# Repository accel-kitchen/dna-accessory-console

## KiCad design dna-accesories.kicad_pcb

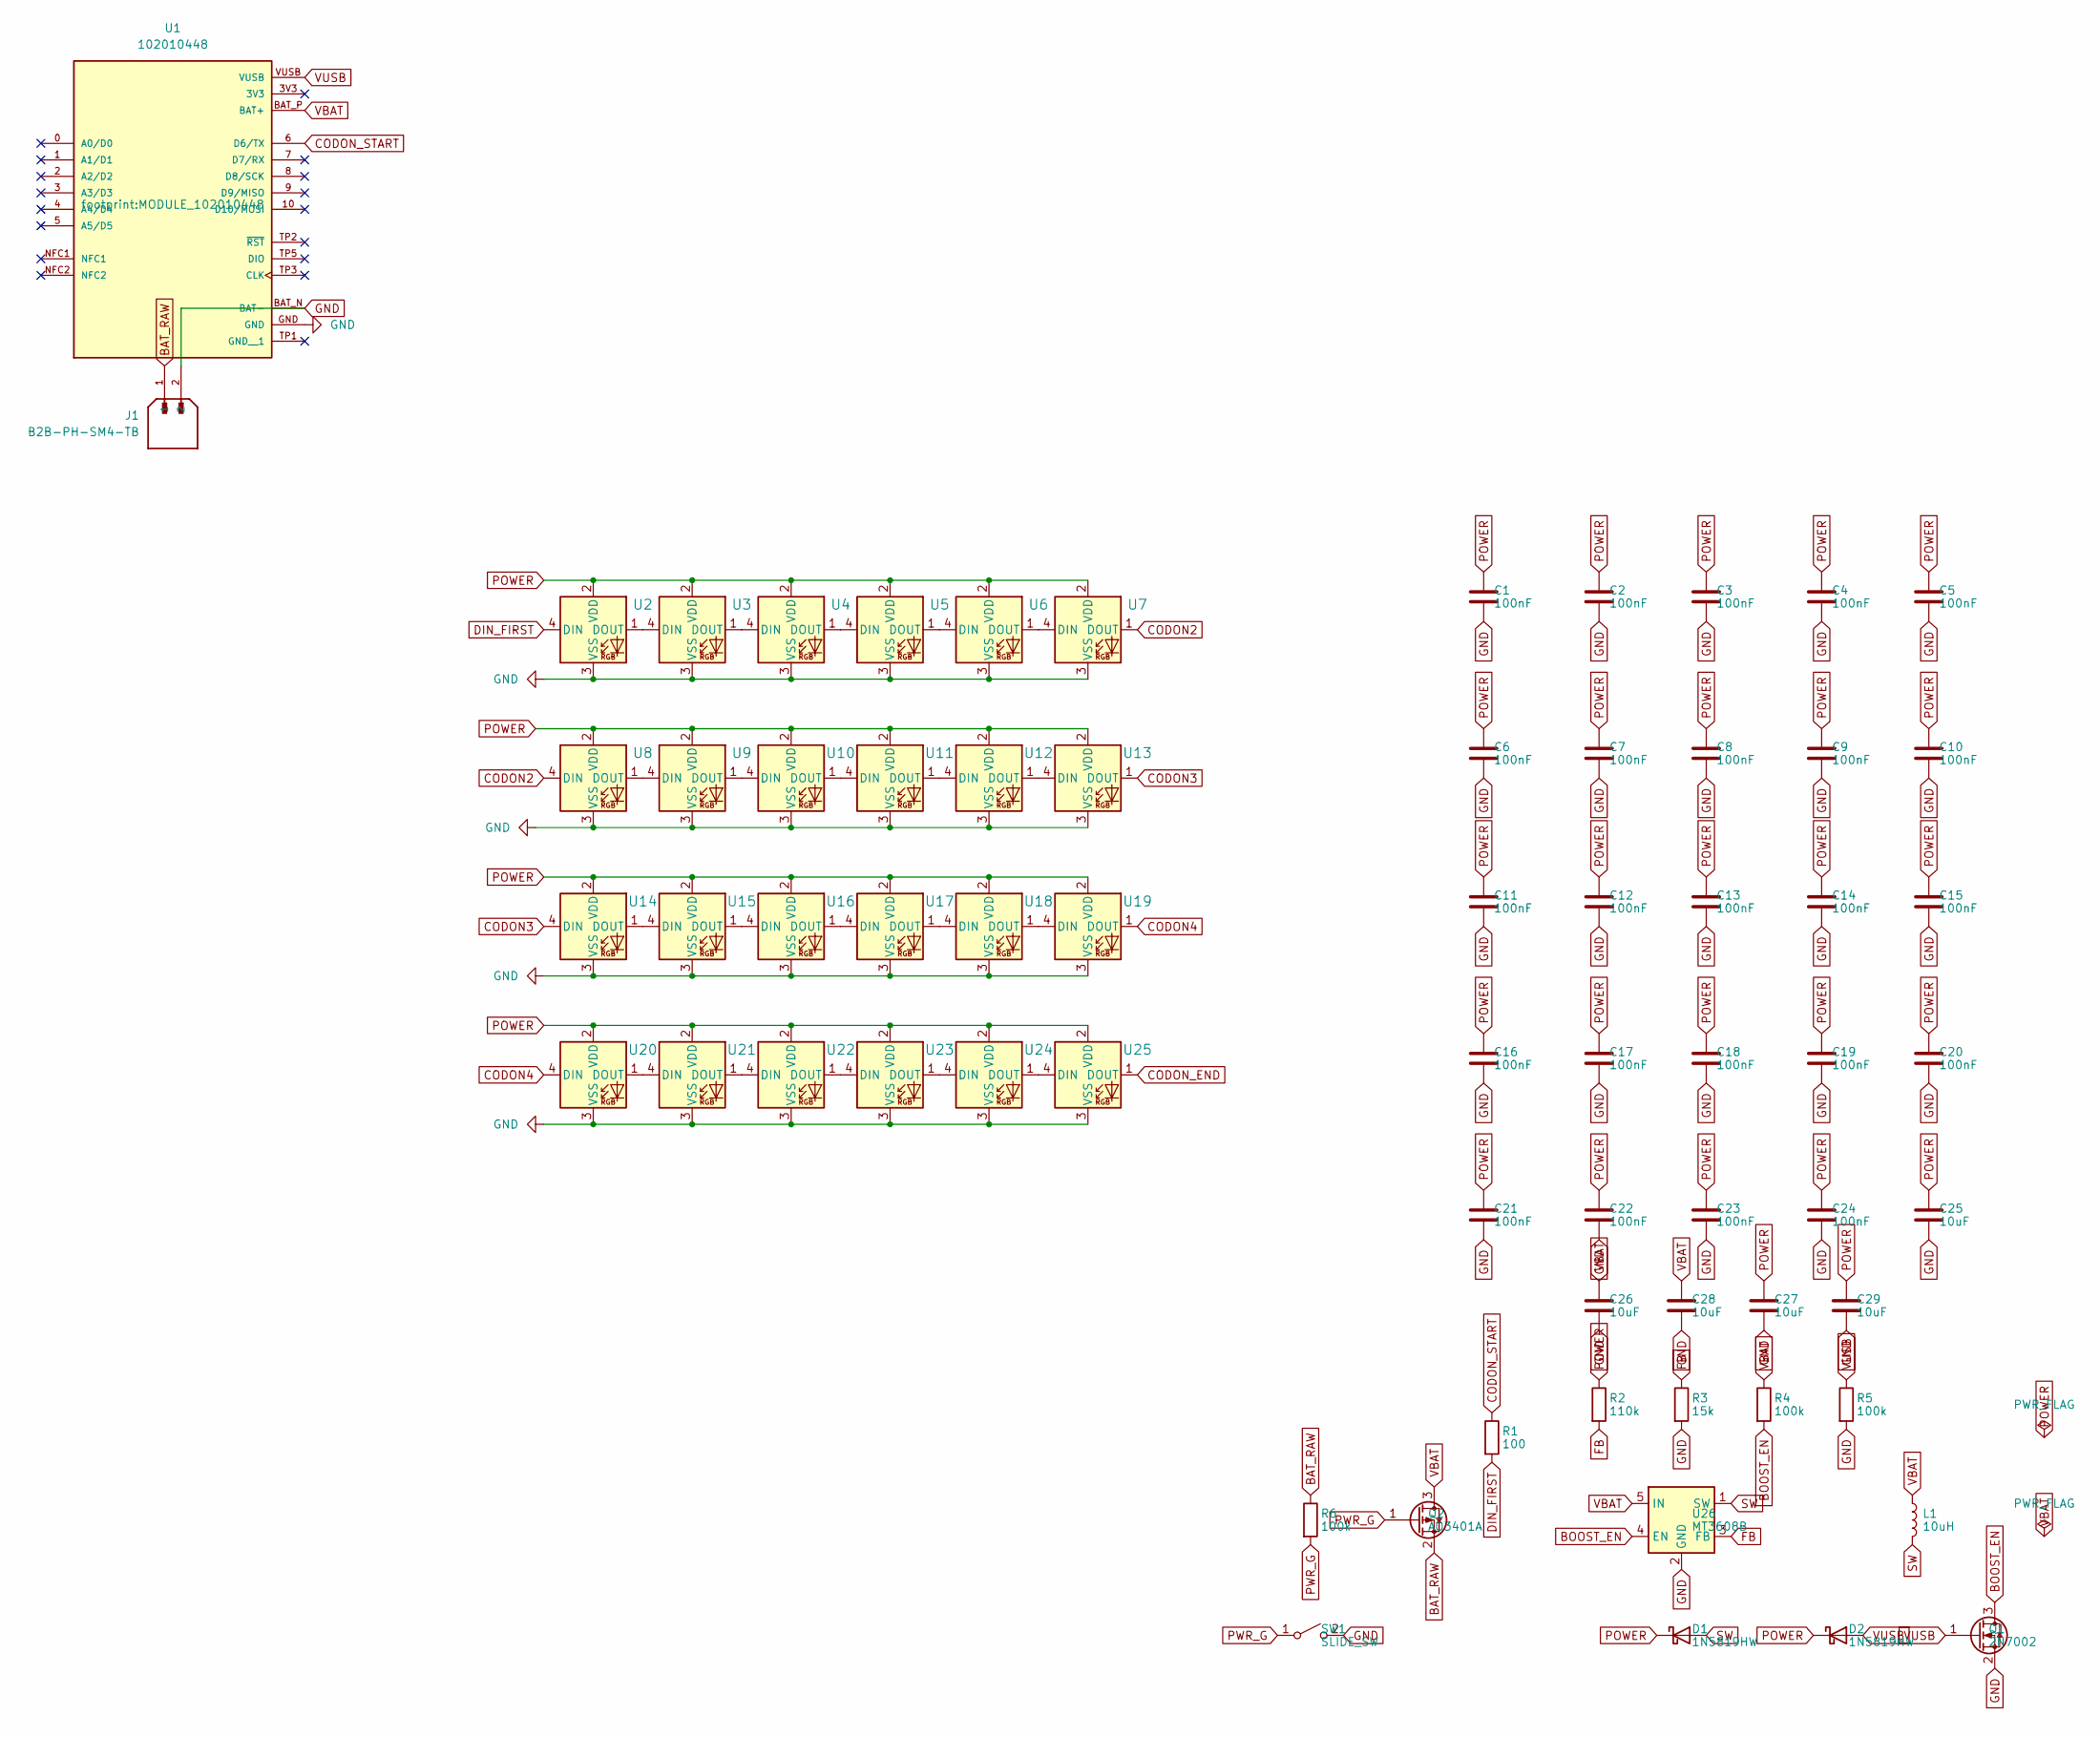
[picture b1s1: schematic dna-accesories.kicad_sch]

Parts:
C1, C2, C3, C4, C5, C6, C7, C8, C9, C10, C11, C12, C13, C14, C15, C16, C17, C18, C19, C20, C21, C22, C23, C24: 100nF; C_0402_1005Metric
C25, C26, C27, C28, C29: 10uF; C_0805_2012Metric
D1, D2: 1N5819HW; D_SOD-123
J1: B2B-PH-SM4-TB; JST_B2B-PH-SM4-TB; PARTREV N/A
L1: 10uH; L_Bourns-SRN4018
Q1: 2N7002; SOT-23
Q2: AO3401A; SOT-23
R1: 100; R_0402_1005Metric
R2: 110k; R_0402_1005Metric
R3: 15k; R_0402_1005Metric
R4, R5, R6: 100k; R_0402_1005Metric
SW1: SLIDE_SW; SW_DIP_SPSTx01_Slide_Copal_CHS-01A_W5.08mm_P1.27mm_JPin
U1: 102010448; MODULE_102010448; PARTREV 2022/08/18
U2, U3, U4, U5, U6, U7, U8, U9, U10, U11, U12, U13, U14, U15, U16, U17, U18, U19, U20, U21, U22, U23, U24, U25: XL-1010RGBC-WS2812B; SMD4_XL-1010RGBC_XLG
U26: MT3608B; SOT-23-6

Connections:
BAT_RAW: J1.1, Q2.2 (S), R6.1
BOOST_EN: Q1.3 (D), R4.2, U26.4 (EN)
CODON2: U7.1 (VDD), U8.4 (DIN)
CODON3: U13.1 (VDD), U14.4 (DIN)
CODON4: U19.1 (VDD), U20.4 (DIN)
CODON_END: U25.1 (VDD)
CODON_START: R1.1, U1.6 (D6/TX)
DIN_FIRST: R1.2, U2.4 (DIN)
FB: R2.2, R3.1, U26.3 (FB)
GND: C1.2, C2.2, C3.2, C4.2, C5.2, C6.2, C7.2, C8.2, C9.2, C10.2, C11.2, C12.2, C13.2, C14.2, C15.2, C16.2, C17.2, C18.2, C19.2, C20.2, C21.2, C22.2, C23.2, C24.2, C25.2, C26.2, C27.2, C28.2, C29.2, J1.2, Q1.2 (S), R3.2, R5.2, SW1.2 (B), U1.BAT_N (BAT-), U1.GND, U2.3 (VSS), U3.3 (VSS), U4.3 (VSS), U5.3 (VSS), U6.3 (VSS), U7.3 (VSS), U8.3 (VSS), U9.3 (VSS), U10.3 (VSS), U11.3 (VSS), U12.3 (VSS), U13.3 (VSS), U14.3 (VSS), U15.3 (VSS), U16.3 (VSS), U17.3 (VSS), U18.3 (VSS), U19.3 (VSS), U20.3 (VSS), U21.3 (VSS), U22.3 (VSS), U23.3 (VSS), U24.3 (VSS), U25.3 (VSS), U26.2 (GND)
unnamed: U2.1 (VDD), U3.4 (DIN)
unnamed: U3.1 (VDD), U4.4 (DIN)
unnamed: U4.1 (VDD), U5.4 (DIN)
unnamed: U5.1 (VDD), U6.4 (DIN)
unnamed: U6.1 (VDD), U7.4 (DIN)
unnamed: U8.1 (VDD), U9.4 (DIN)
unnamed: U9.1 (VDD), U10.4 (DIN)
unnamed: U10.1 (VDD), U11.4 (DIN)
unnamed: U11.1 (VDD), U12.4 (DIN)
unnamed: U12.1 (VDD), U13.4 (DIN)
unnamed: U14.1 (VDD), U15.4 (DIN)
unnamed: U15.1 (VDD), U16.4 (DIN)
unnamed: U16.1 (VDD), U17.4 (DIN)
unnamed: U17.1 (VDD), U18.4 (DIN)
unnamed: U18.1 (VDD), U19.4 (DIN)
unnamed: U20.1 (VDD), U21.4 (DIN)
unnamed: U21.1 (VDD), U22.4 (DIN)
unnamed: U22.1 (VDD), U23.4 (DIN)
unnamed: U23.1 (VDD), U24.4 (DIN)
unnamed: U24.1 (VDD), U25.4 (DIN)
POWER: C1.1, C2.1, C3.1, C4.1, C5.1, C6.1, C7.1, C8.1, C9.1, C10.1, C11.1, C12.1, C13.1, C14.1, C15.1, C16.1, C17.1, C18.1, C19.1, C20.1, C21.1, C22.1, C23.1, C24.1, C25.1, C27.1, C29.1, D1.1 (K), D2.1 (K), R2.1, U2.2 (DOUT), U3.2 (DOUT), U4.2 (DOUT), U5.2 (DOUT), U6.2 (DOUT), U7.2 (DOUT), U8.2 (DOUT), U9.2 (DOUT), U10.2 (DOUT), U11.2 (DOUT), U12.2 (DOUT), U13.2 (DOUT), U14.2 (DOUT), U15.2 (DOUT), U16.2 (DOUT), U17.2 (DOUT), U18.2 (DOUT), U19.2 (DOUT), U20.2 (DOUT), U21.2 (DOUT), U22.2 (DOUT), U23.2 (DOUT), U24.2 (DOUT), U25.2 (DOUT)
PWR_G: Q2.1 (G), R6.2, SW1.1 (A)
SW: D1.2 (A), L1.2, U26.1 (SW)
VBAT: C26.1, C28.1, L1.1, Q2.3 (D), R4.1, U1.BAT_P (BAT+), U26.5 (IN)
VUSB: D2.2 (A), Q1.1 (G), R5.1, U1.VUSB

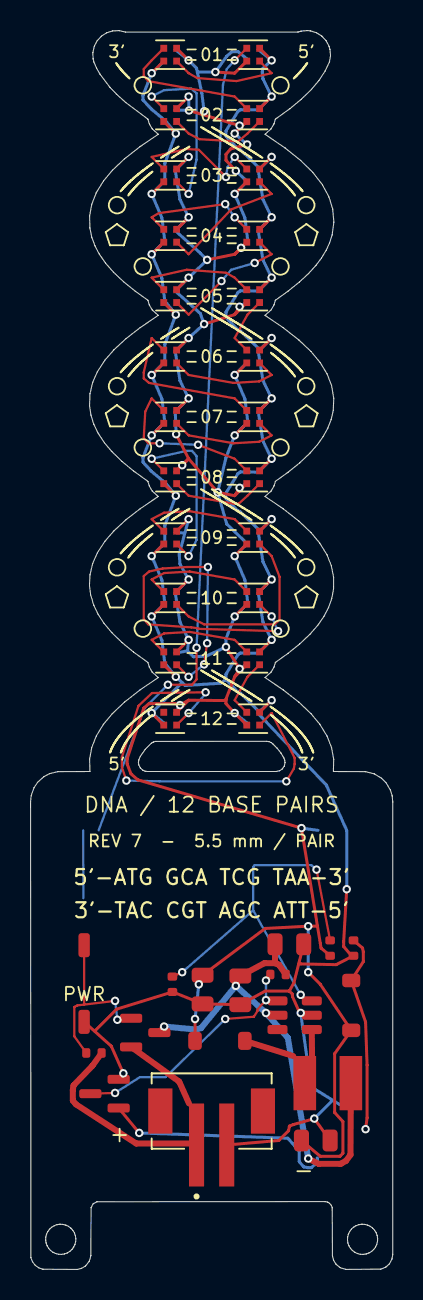
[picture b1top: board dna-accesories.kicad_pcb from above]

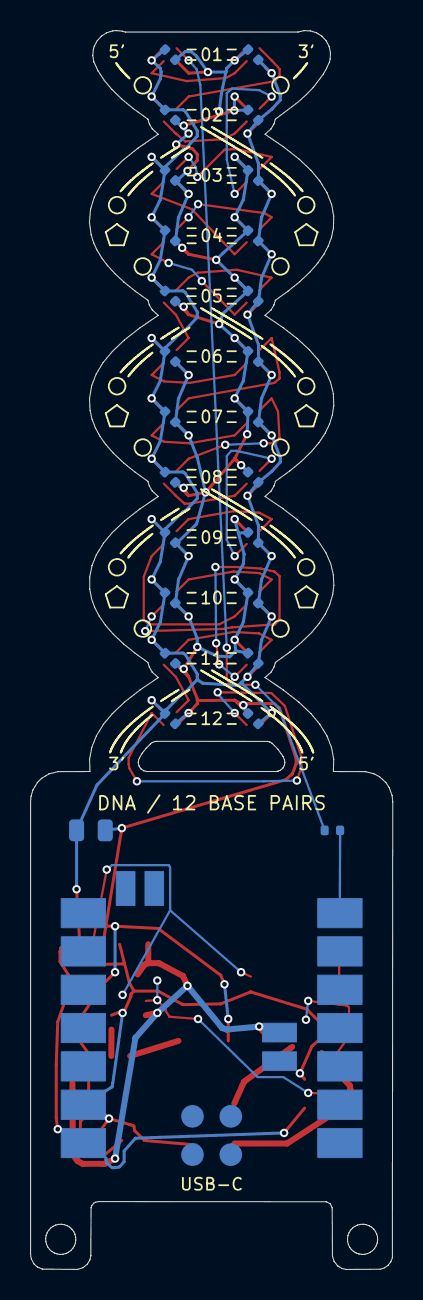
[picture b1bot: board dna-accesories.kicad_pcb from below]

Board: 2 copper layers, 24.0 x 82.1 mm, 68 parts (27 on the bottom side), 34 nets.

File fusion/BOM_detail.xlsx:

Designator | Qty | Value | Description | Package / footprint | Side | Manufacturer | MPN / Seeed SKU | LCSC # | Approved alternate | Assembly note | Link
U1 | 1 | 102010448 | Seeed Studio XIAO nRF52840 (XIAO BLE), plain version without pin headers | 21 x 17.8 mm castellated SMD module / MODULE_102010448 | bottom | Seeed Studio | 102010448 |  |  | Seeed SKU 102010448 (NOT the "Pre-Soldered" variant 102010631). Bottom side of 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 | https://www.seeedstudio.com/Seeed-XIAO-BLE-nRF52840-p-5201.html
J1 | 1 | B2B-PH-SM4-TB | PH-series 2-pin 2.0 mm pitch SMD side-entry wafer, tin plated | SMD, side entry / JST_B2B-PH-SM4-TB | top | JST | B2B-PH-SM4-TB(LF)(SN) | C160352 |  | Battery connector. Pad 1 = BAT+ (left, "+" on the silkscreen), pad 2 = BAT-. Da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 | https://www.lcsc.com/product-detail/image/B2B-PH-SM4-TB-LF-S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
U2,U3,U4,U5,U6,U7,U8,U9,U10,U11,U12,U13,U14,U15,U16,U17,U18,U19,U20,U21,U22,U23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 | 24 | XL-1010RGBC-WS2812B | 1010 RGB LED with built-in WS2812B-type driver, 4-pad | 1.0 x 1.0 mm SMD (4 pad) / SMD4_XL-1010RGBC_XLG | top | XINGLIGHT | XL-1010RGBC-WS2812B | C5349953 |  | Orientation-sensitive (pad 1 = DOUT). MSL: confirm with the reel label and bake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 | https://www.lcsc.com/product-detail/Light-Emitting-Diodes-LE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
U26 | 1 | MT3608B | 1.2 MHz step-up converter, 2.5-24 V in, 4 A switch, adjustable output, SOT-23-6 | SOT-23-6 / SOT-23-6 | top | Aerosemi | MT3608B |  | MT3608 (same SOT-23-6 pinout: 1 SW, 2 GND, 3 FB, 4 EN, 5 VIN, 6 NC) | Pin 1 = SW (see detail E). Output 5.0 V = 0.6 V x (1 + 110k/15k). Battery to LE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 | https://www.lcsc.com/search?q=MT3608B
L1 | 1 | 10uH | Shielded power inductor 10 uH, Irms 1.2 A, Isat 1.3 A, DCR 0.15 ohm max, 4.0 x 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 | 4.0 x 4.0 mm SMD / L_Bourns-SRN4018 | top | Bourns | SRN4018TA-100M |  | Sunlord SWPA4020S100MT (LCSC C82398; 10 uH, Irms 0.9 A, Isat 1.6 A, 4 x 4 x 2 m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 | Non-polarized. Boost inductor: carries up to ~0.8 A at full white on a 3.0 V ce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 | https://www.digikey.com/en/products/result?keywords=SRN4018TA-100M
D1,D2 | 2 | 1N5819HW | Schottky diode 40 V 1 A, SOD-123 | SOD-123 / D_SOD-123 | top | Diodes Incorporated | 1N5819HW-7-F | C82544 | Any SOD-123 Schottky, 40 V, 1 A, Vf <= 0.5 V at 1 A | Polarized: cathode (bar) at pad 1. D1 = boost rectifier, D2 = USB to LED power 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 | https://lcsc.com/product-detail/Schottky-Diodes_Diodes-Incor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
Q1 | 1 | 2N7002 | N-channel MOSFET 60 V 210 mA, SOT-23 | SOT-23 / SOT-23 | top | Diodes Incorporated | 2N7002-7-F | C85049 | 2N7002K-7 (LCSC C85047) | Pin 1 = gate, 2 = source, 3 = drain. Pulls the boost EN pin low while USB is pr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 | https://www.lcsc.com/product-detail/C85049.html
C25,C26,C27,C28,C29 | 5 | 10uF | MLCC 10 uF 25 V X5R +/-10 % 0805 | 0805 (2012 metric) / C_0805_2012Metric | bottom/top | Samsung Electro-Mechanics | CL21A106KAYNNNE | C15850 | Murata GRM21BR61E106KA73L (same value/voltage/dielectric) | Non-polarized. Bulk capacitor on the 5 V rail. | https://www.lcsc.com/product-detail/C15850.html
C1,C2,C3,C4,C5,C6,C7,C8,C9,C10,C11,C12,C13,C14,C15,C16,C17,C18,C19,C20,C21,C22,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 | 24 | 100nF | MLCC 100 nF 25 V X7R +/-10 % 0402 | 0402 (1005 metric) / C_0402_1005Metric | bottom | Samsung Electro-Mechanics | CL05B104KA5NNNC |  | Murata GRM155R71E104KE14D (same value/voltage/dielectric) | Non-polarized. One per LED, back side, directly behind the LED. | https://www.digikey.com/en/products/detail/samsung-electro-m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
R1 | 1 | 100 | Thick-film resistor 100 ohm 1 % 1/16 W 0402 | 0402 (1005 metric) / R_0402_1005Metric | bottom | Yageo | RC0402FR-07100RL | C106232 | UNI-ROYAL 0402WGF1000TCE | Series resistor in the LED data line (XIAO D6 -> U2 DIN). | https://www.lcsc.com/product-detail/C106232.html
R2 | 1 | 110k | Thick-film resistor 110 kohm 1 % 1/16 W 0402 | 0402 (1005 metric) / R_0402_1005Metric | top | Yageo | RC0402FR-07110KL |  | Any 0402 110 kohm 1 % | Boost feedback divider (top): 5.0 V output with R3 = 15 kohm. | https://www.lcsc.com/search?q=RC0402FR-07110KL
R3 | 1 | 15k | Thick-film resistor 15 kohm 1 % 1/16 W 0402 | 0402 (1005 metric) / R_0402_1005Metric | top | Yageo | RC0402FR-0715KL |  | Any 0402 15 kohm 1 % | Boost feedback divider (bottom). | https://www.lcsc.com/search?q=RC0402FR-0715KL
R4,R5,R6 | 3 | 100k | Thick-film resistor 100 kohm 1 % 1/16 W 0402 | 0402 (1005 metric) / R_0402_1005Metric | top | Yageo | RC0402FR-07100KL |  | Any 0402 100 kohm | R4: boost EN pull-up to the battery. R5: gate pull-down of Q1. R6: gate pull-up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 | https://www.lcsc.com/search?q=RC0402FR-07100KL
Q2 | 1 | AO3401A | P-channel MOSFET -30 V -4 A, Rds(on) 60 mohm at Vgs -4.5 V, SOT-23 | SOT-23 / SOT-23 | top | Alpha & Omega Semiconductor | AO3401A |  | Any SOT-23 P-MOSFET with pinout 1 gate / 2 source / 3 drain, Vgs(th) <= -1.3 V,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 | Q2 = battery power switch. Pin 1 = gate, 2 = source (battery side, J1 pad 1), 3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 | https://www.lcsc.com/search?q=AO3401A
SW1 | 1 | SLIDE_SW | 1-position SPST SMD slide (DIP-type) switch, J-hook terminals, 5.08 mm span, 10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 | SMD, J-hook, 7.3 x 3.3 mm / SW_DIP_SPSTx01_Slide_Copal_CHS-01A_W5.08mm_P1.27mm_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 | top | Nidec Copal | CHS-01A | C132834 | Any 1-position SMD slide switch with J-hook leads and 5.08 mm lead span (KiCad 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 | SW1 = power switch: it only switches the gate of Q2 (microamps), not the batter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 | https://lcsc.com/product-detail/DIP-Switches_Nidec-CHS-01A_C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

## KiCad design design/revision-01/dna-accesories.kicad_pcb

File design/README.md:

# DNA二重らせん基板：外形・配置の改訂版2

2026-10-08。主ファイル `../dna-accesories.kicad_pcb` を更新。

- 約29.0 × 116.6 mm、2本の鎖・12本の塩基対、吊り下げ穴φ3 mm。
- U2/U3、U4/U5、…、U24/U25の12対。LEDは1個ずつ塩基を表す。
- 全12対でLED中心間を10.0 mmに統一。LED本体1.0 mmを基準にした本体間隔は約9.0 mm。
- 表面シルクに二重線の鎖、交差部の重なり、塩基間の破線、5′・3′方向と対番号を記載。
- 各対内DOUT→DINを配線し、その他の配線は未完了。
- U1は裏面、J1は表面。LEDの型番・端子・ネット・UUIDは維持。
- らせんは装飾用の投影モデル。分子スケールの比率は表していない。
- LED/モジュールのローカルフットプリントはシルクだけを整理。パッドとモデルは維持。

## 確認済み

書き込み・読み戻し・削除に成功。KiCad 9.0.4で配置段階のDRCを実行し、違反0件、回路図との対応差異0件。未接続は別枠で62件あり、全配線完了を意味しない。

## 次工程

電源/GND、各対の間、電池・モジュール間の配線。電池単独でのLED給電、LED近傍コンデンサ、信号保護、採用品の端子位置照合。製造前に配線と電源設計を完成し、最終DRC・実装図・製造データを確認する。

## ファイル

- `base-pairs.csv`: 塩基対とLEDの対応・座標・ネット。
- `placement-drc.json`: 配置段階のDRCと未接続。
- `net-preservation.json`: 更新前後で部品UUIDとパッドネットが一致することの記録。
- `preview/dna-layout.svg`, `.png`: 実座標の配置図。色は鎖の識別用。
- `front-silkscreen.json`: 実PCBの表面シルクを抽出した描画データ。プレビューの白線はこの実データを使用。
- `preview/front-kicad.svg`, `back-kicad.svg`: 実PCBから出力した図。
- `pre-redesign-20261008/`: 改訂前のPCB・回路図・プロジェクト・ライブラリ表と変更したフットプリントのバックアップ。
- `revision-01/`: LED間隔変更前の外形・配置版のバックアップ。
- `../review.html`: 改訂5の基板レビュー（配線・ネット・電源・製造余裕・3D干渉を実測）。旧レビュー（改訂3＋改訂4の追記）は `review-rev3-rev4.html`。生成は `gen/review_checks.py` → `gen/make_review.py`。`gen/build_functional_review.py` は旧レビュー用（出力先を `review-rev3-rev4.html` に変更済み）。
- `functional-review/`: 再実行DRC/ERC、ネットリスト、対象ファイルのハッシュ、メーカー資料の保存版。
- `layout-review.html`: 配置プレビュー生成時に出力する配置説明。主レビューは上書きしない。

## 再生成

Python 3.13とShapely 2.2.0を使用。KiCad側スクリプトはKiCad付属Pythonで実行する。

```powershell
python gen/make_dna_geometry.py --dependency-path '<Shapelyインストール先>'
& 'C:\Program Files\KiCad\9.0\bin\python.exe' gen/clean_footprint_silk.py
& 'C:\Program Files\KiCad\9.0\bin\python.exe' gen/rebuild_dna_board.py
& 'C:\Program Files\KiCad\9.0\bin\kicad-cli.exe' pcb drc --schematic-parity --format json -o design/placement-drc.json dna-accesories.kicad_pcb
```

再生成はバックアップPCBを起点にするため、この改訂後に手作業で編集した配線は上書きされる。

動作レビューのHTMLは `python gen/build_functional_review.py` で再生成できる。`functional-review/summary.json` に記録したファイルハッシュと現設計が一致しない場合は生成を停止する。PCBを変更したら、DRC/ERC・ネットリスト・集計を再実行してレビュー内容も見直すこと。

## 改訂3（2026-10-10）

- 表裏のシルクを追加：塩基文字（配列 ATG GCA TCG TAA と相補鎖）、水素結合（A-T 2本／G-C 3本）、糖・リン酸の環、吊り下げ穴リング、配列・凡例、裏面のUSB-C目印。再生成は `DNA_DEPS=<Shapely>` を指定して `gen/rebuild_dna_board.py`。
- U1（XIAO）とJ1にSTEPを設定し、全26部品が3Dモデルを持つ。`gen/check_interference.py` で干渉計算（`interference-check.json`）。部品間・基板との重なりは0件。USB-Cプラグ（仮寸法）は基板下端に食い込むため `review-rev3-rev4.html` の指摘09（改訂4で解消、改訂5の `review.html` で再確認）。
- 更新前の状態：`pre-silk-20261010/`。DRC違反0件、未接続62件は変わらず。

## 改訂4：配線（2026-10-10）

- `review-rev3-rev4.html` の指摘01に従い、LEDのVDD/DOUTを入れ替え（VDD=2番、DOUT=1番。`gen/swap_led_pins.py`。シンボル位置は不変）。
- POWER・GND・24段データ・J1とBAT端子を2層で配線（`gen/route_prep.py` → `gen/route_board.py` → `gen/route_apply.py`）。KiCad 9.0.4：DRC違反0、未接続0、回路図差異0（`wiring-drc.json`）。ERCは警告1件（`wiring-erc.json`。ここに書いていた「26件」は誤りで、10月10日のファイルも1件）。
- 未対応：電池単独給電、LED近傍コンデンサ、DIN直列抵抗の場所、USB-C干渉（review指摘03〜09）。
- 配線前のバックアップ：`pre-wiring-20261010/`。旧レビューは先頭に注記のみ追加し、本文は配線前の状態（現在は `review-rev3-rev4.html`）。`rebuild_dna_board.py` を再実行すると配線は消える。
- 配線ルータは自作のグリッド探索で乱数順序（SEED）を使うため、結果の再現には `gen/_routes.json` を使用する。

## 発注用データ（2026-10-10）

- `../fusion/` に Seeed Fusion PCBA 用のガーバー zip・BOM・位置ファイル・実装図・手順を作成。詳細は `../fusion/README.md`。

## 改訂5：らせんの縮小・吊り穴の移動・塩基文字の削除（2026-11-02〜03）

- 外形 29.0 × 116.6 mm → 24.0 × 82.1 mm。マイコン部の幅は29 → 24 mm（XIAOのパッドが約20 mm）。
  らせん部（先端〜襟）は88.1 mm → 49.1 mm、うち12対の間隔の合計は78 → 48 mm（12 × 4.0 mm）。らせんの幅は26.8 → 16.2 mm。
  LED間隔 10 → 5.5 mm、塩基対ピッチ 6.5 → 4.0 mm、梁幅 3.0 mm、バックボーン幅 3.2 mm、振幅 6.5 mm。
  これ以上詰める限界の目安：ピッチ3.8 mmは配線が収束しにくく（銅箔〜外形 0.56 mm では未接続が残った）、3.6 mm以下は梁幅2.8 mm以下になりLED周りのビアが入らない。
  ピッチ4.9 mm以下では抜き穴がほぼ消える（外形は梁のふくらみだけでらせんに見える）。
- 吊り穴：らせん先端のφ3 mm を廃止し、マイコン部下端（USB-C側）の外側に、左右2つの耳（幅4 mm、長さ約4.5 mm）を延ばしてφ2.0 mm の穴を各1つ。
  耳の内側の間隔は16 mmで、USB-Cプラグはその間を通る。USB-C側を上にして吊る。
- シルク：各段の塩基文字（T/C/A/G）を削除。対番号は中央に移動し、水素結合の破線は左右に分けた。
  配列2行・START/STOP・凡例・水素結合の本数は従来どおり。
- 再生成手順：`gen/make_dna_geometry.py` → `gen/rebuild_dna_board.py`（起点は `pre-compact-20261102/` の配線済み基板）
  → `gen/route_prep.py`（--swapは付けない）→ `gen/route_board.py`（`WS=0.15 CL=0.16 WP=0.2 EDGE=0.56 VIAD=0.56`、失敗したネットを `PRIO` で先頭へ送って再試行）→ `gen/route_apply.py`。
  寸法は環境変数 `DNA_D / DNA_P / DNA_A / DNA_RAIL / DNA_RUNG` で変えられる。Shapelyは `gen/_deps/py313`（通常Python）と `gen/_deps/py311`（KiCad付属Python、`DNA_DEPS`）。
  `EDGE` を0.55以下にすると、ラスタ化の誤差で銅箔〜外形が0.5 mmを割る（DRCの銅箔外形エラー）ので0.56を使う。
- KiCad 9.0.4：DRC違反0、未接続0、回路図差異0（`wiring-drc.json`）。
- 更新前の状態：`pre-compact-20261102/`。`base-pairs.csv` の `base` 列は配列上の塩基で、シルクには出ていない。
- 発注データ（`../fusion/`）は改訂5に合わせて再生成済み（`gen/dump_assembly_data.py` → `gen/make_fusion_package.py`）。
- 試作ページ `../lp/` は `gen/make_lp_images.py` で、画像（3Dレンダリング）とLED座標の対応を再生成する。

## 新旧の比較資料

`comparison-rev4-rev5.html`（1ファイルで開ける）：改訂4（`pre-compact-20261102/`）と現在の基板を、同縮尺の3D画像・外形の重ね図・数値表で比較。
再生成：`gen/compare_stats.py`（KiCad付属Python）→ `gen/make_comparison.py`。

## 改訂5のレビュー（2026-11-06、`review-rev5.html`）

`../review.html`。DRC・ERCに加え、厳しい規則のDRCで間隔を実測、基板のトラックから電源の電圧降下を計算、ネット連鎖と部品位置を照合、3D干渉と製造データ（ガーバー・ドリル・BOM・実装座標）を確認。結論：配線・形状・製造データに誤りなし。未解決は「電池単独でLEDが点灯しない」（設計判断）。吊り穴まわりの肉厚1.0 mm、ビア環0.13 mmは確認をすすめる。

## 改訂6：電池でも LED が光る（2026-11-06）

- 改訂5の未解決点（LED の電源が USB の 5 V だけ）に対し、昇圧と USB／電池の自動切り替えを追加。
  電池（VBAT）→ L1 → MT3608B（U26）→ D1 → POWER（5.0 V）。USB があるときは USB → D2 → POWER、Q1 が U26 の EN を落として昇圧を止める。
  出力電圧は 0.6 V × (1 + R2/R3) = 5.0 V（110 kΩ／15 kΩ、データシート Fig.1 の値）。部品 13 点（U26、L1、D1、D2、Q1、C26〜C29、R2〜R5）は襟の表面。
  電池のマイナス（J1.2・XIAO の BAT−）は GND に直結（Seeed 回路図 v1.1 で BAT− は GND）。
- 回路図：`gen/add_boost_sch.py`（1 回だけ実行。起点は `pre-boost-20261106/`）。基板：`gen/place_boost.py`（配置の探索、結果は `gen/_boost_place.json`）
  → `gen/add_boost_pcb.py`（`boost-base/` を作る）→ `gen/rebuild_dna_board.py`（起点は `boost-base/`）→ `gen/route_prep.py` → `gen/route_search.py`（シードを変えて並列）→ `gen/route_apply.py`。
  ルーターは、VBAT・SW を 0.4 mm、電源・GND・VUSB を 0.2 mm、信号を 0.15 mm で引き、XIAO のフットプリントの禁止領域（テストパッド周り）を避ける。
- シルク：襟の表面は昇圧部品の場所をあけるため、START/STOP と凡例 3 行を削除。REV は「REV 6」。
- 検証：KiCad 9.0.4 の DRC 違反 0・未接続 0・回路図差異 0。ERC は警告 3 件（ラベル 1、BAT−／BAT＋の端子の型の組み合わせ 2）。銅箔間隔の最小 0.143 mm、銅箔〜外形 0.560 mm。3D 干渉 0。
- ファームウェア（`../console/firmware/`、`../firmware/`）：USB 給電がないときに D6 を浮かせる処理を削除。
- 発注データ（`../fusion/`）は 65 点・13 品番で再生成。実装図に昇圧部の拡大図（Detail E）を追加。
- 実機での昇圧回路の動作は未確認。レビューは `../review.html`、改訂4との比較は `comparison-rev4-rev5.html`。
- 更新前の状態：`pre-boost-20261106/`。

## 改訂7：電池の電源スイッチ（2026-11-07、`../review.html`）

- 改訂6では電池が消灯中も昇圧と LED の待機電流（概算 約 19 mA）で減り続けるため、電池と回路の間に電源スイッチを追加した。
  小型の SMD スライドスイッチは定格 50〜300 mA で電池の電流（最大 約 0.73 A）を流せないため、**スイッチは P-MOSFET のゲートだけを切り替える**。
  J1.1（ネット BAT_RAW）→ Q2（AO3401A）のソース、Q2 のドレイン → VBAT（XIAO の BAT＋、昇圧の入力）、R6（100 kΩ）がゲートをソースに引き上げ（OFF）、SW1（Nidec Copal CHS-01A、DIP 型スライド）がゲートを GND に落とす（ON）。
  OFF では電池の電流がほぼ 0。OFF で USB を挿すと、Q2 のボディダイオード経由で電池は 3.5 V 程度までしか充電されない（満充電は ON）。
- 追加部品 3 点（SW1、Q2、R6）は襟の表面の左側。回路図は J1.1 と XIAO の BAT＋をつないでいた配線を切り、ラベルで BAT_RAW と VBAT に分けた。シルクは「REV 7」と電源スイッチのそばの「PWR」。
- 再生成：`gen/add_boost_sch.py`（起点は `pre-boost-20261106/`。昇圧と電源スイッチを一度に追加）→ `gen/place_boost.py`（16 部品の配置探索。結果は `gen/_boost_place.json`）
  → `gen/add_boost_pcb.py` → `gen/rebuild_dna_board.py` → `gen/route_prep.py` → `gen/route_search.py`（シードを多数並列。今回は 22 本中、シード 61 が全ネットを配線）→ `gen/route_apply.py`。
  `gen/route_board.py` の配線クラスは、BAT_RAW・VBAT・SW を 0.4 mm にした。
- 検証：KiCad 9.0.4 の DRC 違反 0・未接続 0・回路図差異 0。ERC は警告 3 件（改訂6と同じ）。銅箔間隔の最小 0.131 mm、銅箔〜外形 0.602 mm（`gen/strict_drc.py` で実測）。3D 干渉は 68 部品で 0。
  電池〜昇圧入力の降下は、3.0 V・0.73 A で 約 93 mV（Q2 のオン抵抗を 85 mΩ と置いた見積りを含む）。
- 発注データ（`../fusion/`）は 68 点・15 品番で再生成。実装図に電源スイッチの拡大図（Detail F）を追加。3D 画像（`../lp/assets/img/`）・試作ページ・比較資料も更新。
- 実機での昇圧回路と電源スイッチの動作は未確認。AO3401A の LCSC 番号と Rds(on)、SW1 の ON の向き（本体の表示に従う）は要確認。
- 更新前の状態：`pre-switch-20261106/`（`.gitignore` の対象）。旧レビュー：`review-rev6.html`。

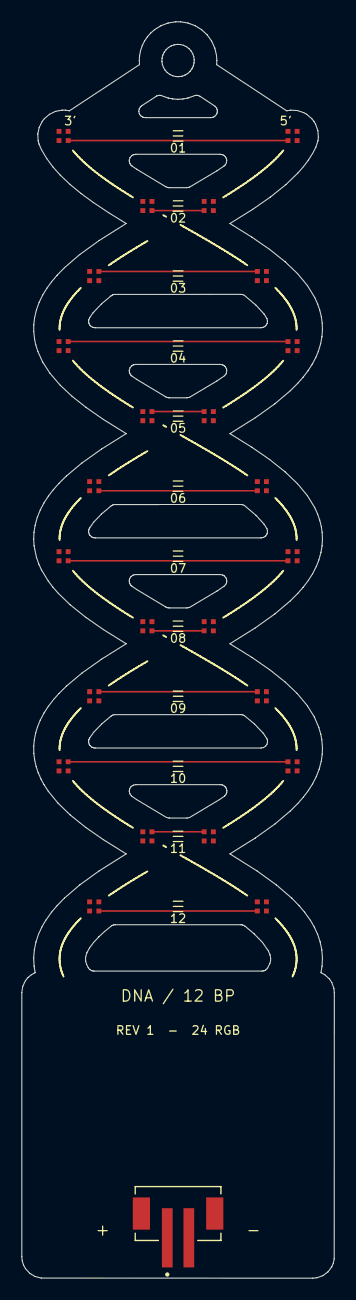
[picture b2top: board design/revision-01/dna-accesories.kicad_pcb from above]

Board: 2 copper layers, 29.0 x 116.6 mm, 26 parts (1 on the bottom side), 28 nets.

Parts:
J1: B2B-PH-SM4-TB; JST_B2B-PH-SM4-TB
U1: 102010448; MODULE_102010448
U2, U3, U4, U5, U6, U7, U8, U9, U10, U11, U12, U13, U14, U15, U16, U17, U18, U19, U20, U21, U22, U23, U24, U25: XL-1010RGBC-WS2812B; SMD4_XL-1010RGBC_XLG

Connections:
CODON2: U7.2 (DOUT), U8.4 (DIN)
CODON3: U13.2 (DOUT), U14.4 (DIN)
CODON4: U19.2 (DOUT), U20.4 (DIN)
CODON_START: U1.6 (D6/TX), U2.4 (DIN)
GND: U1.GND, U2.3 (VSS), U3.3 (VSS), U4.3 (VSS), U5.3 (VSS), U6.3 (VSS), U7.3 (VSS), U8.3 (VSS), U9.3 (VSS), U10.3 (VSS), U11.3 (VSS), U12.3 (VSS), U13.3 (VSS), U14.3 (VSS), U15.3 (VSS), U16.3 (VSS), U17.3 (VSS), U18.3 (VSS), U19.3 (VSS), U20.3 (VSS), U21.3 (VSS), U22.3 (VSS), U23.3 (VSS), U24.3 (VSS), U25.3 (VSS)
unnamed: J1.1, U1.BAT_P (BAT+)
unnamed: J1.2, U1.BAT_N (BAT-)
unnamed: U2.2 (DOUT), U3.4 (DIN)
unnamed: U3.2 (DOUT), U4.4 (DIN)
unnamed: U4.2 (DOUT), U5.4 (DIN)
unnamed: U5.2 (DOUT), U6.4 (DIN)
unnamed: U6.2 (DOUT), U7.4 (DIN)
unnamed: U8.2 (DOUT), U9.4 (DIN)
unnamed: U9.2 (DOUT), U10.4 (DIN)
unnamed: U10.2 (DOUT), U11.4 (DIN)
unnamed: U11.2 (DOUT), U12.4 (DIN)
unnamed: U12.2 (DOUT), U13.4 (DIN)
unnamed: U14.2 (DOUT), U15.4 (DIN)
unnamed: U15.2 (DOUT), U16.4 (DIN)
unnamed: U16.2 (DOUT), U17.4 (DIN)
unnamed: U17.2 (DOUT), U18.4 (DIN)
unnamed: U18.2 (DOUT), U19.4 (DIN)
unnamed: U20.2 (DOUT), U21.4 (DIN)
unnamed: U21.2 (DOUT), U22.4 (DIN)
unnamed: U22.2 (DOUT), U23.4 (DIN)
unnamed: U23.2 (DOUT), U24.4 (DIN)
unnamed: U24.2 (DOUT), U25.4 (DIN)
POWER: U1.VUSB, U2.1 (VDD), U3.1 (VDD), U4.1 (VDD), U5.1 (VDD), U6.1 (VDD), U7.1 (VDD), U8.1 (VDD), U9.1 (VDD), U10.1 (VDD), U11.1 (VDD), U12.1 (VDD), U13.1 (VDD), U14.1 (VDD), U15.1 (VDD), U16.1 (VDD), U17.1 (VDD), U18.1 (VDD), U19.1 (VDD), U20.1 (VDD), U21.1 (VDD), U22.1 (VDD), U23.1 (VDD), U24.1 (VDD), U25.1 (VDD)

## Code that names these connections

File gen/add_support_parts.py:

"""Schematic additions for review items 04 / 05 / 08 (plain python, text edit of the .kicad_sch).

* C1..C24: 100 nF across every LED VDD/GND (datasheet p.7), C25: 10 uF bulk on POWER/GND
* R1: 100 ohm in series between D6 and the first LED DIN (net CODON_START | DIN_FIRST)
* U1: pin types for VUSB / GND / BAT corrected, no-connect flags on unused pins
"""
import re, uuid, json, sys
ROOT = r'D:\Document\Research\software\pcb\dna-accesories'
SCH = ROOT + r'\dna-accesories.kicad_sch'
LIB = ROOT + r'\lib\102010448\102010448.kicad_sym'
DEV = r'C:\Program Files\KiCad\9.0\share\kicad\symbols\Device.kicad_sym'
PROJ_UUID = '39a00d90-ab18-44df-86d9-cc83da3529d4'
uid = lambda: str(uuid.uuid4())


def block(text, start):
    """text of the parenthesised expression that begins at index start"""
    depth = 0
    for i in range(start, len(text)):
        c = text[i]
        if c == '(':
            depth += 1
        elif c == ')':
            depth -= 1
            if depth == 0:
                return text[start:i + 1]
    raise ValueError


def lib_symbol(name):
    d = open(DEV, encoding='utf8').read().replace('\r\n', '\n')
    i = d.index('\t(symbol "%s"\n' % name) + 1
    b = block(d, i)
    b = b.replace('(symbol "%s"' % name, '(symbol "Device:%s"' % name, 1)
    return '\n'.join('\t' + l if k else l for k, l in enumerate(b.split('\n')))  # indent one more level


def set_pin_types(text, changes):
    """changes: {pin number: new electrical type} inside the XIAO symbol"""
    a = text.index('(symbol "XIAO_NRF52840:102010448"') if 'XIAO_NRF52840:102010448"' in text else 0
    out = text; pos = a
    for m in list(re.finditer(r'\(pin (\w+) (?:line|clock|inverted|inverted_clock)', text[a:])):
        s = a + m.start(); b = block(text, s)
        num = re.search(r'\(number "([^"]+)"', b).group(1)
        if num in changes:
            nb = b.replace('(pin %s ' % m.group(1), '(pin %s ' % changes[num], 1)
            out = out.replace(b, nb, 1)
    return out


def xiao_pins(text):
    a = text.index('(symbol "XIAO_NRF52840:102010448"')
    pins = []
    seg = block(text, a)
    for m in re.finditer(r'\(pin (\w+) (?:line|clock|inverted|inverted_clock)', seg):
        m = type('M', (), {'start': lambda self, mm=m: mm.start()})()
        s = a + m.start(); b = block(text, s)
        at = re.search(r'\(at ([-\d.]+) ([-\d.]+) (\d+)\)', b)
        pins.append(dict(num=re.search(r'\(number "([^"]+)"', b).group(1), name=re.search(r'\(name "([^"]+)"', b).group(1),
                         x=float(at.group(1)), y=float(at.group(2))))
    return pins


def main():
    t = open(SCH, encoding='utf8', newline='').read().replace('\r\n', '\n')
    if 'Device:C' in t:
        sys.exit('already applied')
    # 1) library symbols for C and R
    t = t.replace('\t(lib_symbols\n', '\t(lib_symbols\n' + lib_symbol('C') + '\n' + lib_symbol('R') + '\n', 1)
    # 2) U1 pin types; NC flags
    types = {'VUSB': 'power_out', 'GND': 'power_out', 'BAT_P': 'bidirectional', 'BAT_N': 'bidirectional'}
    t = set_pin_types(t, types)
    ux, uy = -2.54, -29.21
    nc_nums = ['0', '1', '2', '3', '4', '5', '7', '8', '9', '10', 'NFC1', 'NFC2', 'TP1', 'TP2', 'TP3', 'TP5', '3V3']
    pins = {p['num']: p for p in xiao_pins(t)}
    extra = []
    for n in nc_nums:
        p = pins[n]
        extra.append('\t(no_connect\n\t\t(at %.2f %.2f)\n\t\t(uuid "%s")\n\t)' % (ux + p['x'], uy - p['y'], uid()))
    # 3) parts
    def label(name, x, y, ang):
        j = 'left' if ang in (90, 0) else 'right'
        return ('\t(global_label "%s"\n\t\t(shape input)\n\t\t(at %.2f %.2f %d)\n\t\t(effects\n\t\t\t(font\n\t\t\t\t(size 1.27 1.27)\n\t\t\t)\n\t\t\t(justify %s)\n\t\t)\n'
                '\t\t(uuid "%s")\n\t\t(property "Intersheetrefs" "${INTERSHEET_REFS}"\n\t\t\t(at %.2f %.2f 0)\n\t\t\t(effects\n\t\t\t\t(font\n\t\t\t\t\t(size 1.27 1.27)\n\t\t\t\t)\n\t\t\t\t(hide yes)\n\t\t\t)\n\t\t)\n\t)'
                % (name, x, y, ang, j, uid(), x, y))

    def part(lib, ref, value, fp, x, y, uu):
        def prop(k, v, dx, dy, hide):
            return ('\t\t(property "%s" "%s"\n\t\t\t(at %.2f %.2f 0)\n\t\t\t(effects\n\t\t\t\t(font\n\t\t\t\t\t(size 1.27 1.27)\n\t\t\t\t)\n%s\t\t\t)\n\t\t)\n'
                    % (k, v, x + dx, y + dy, '\t\t\t\t(hide yes)\n' if hide else '\t\t\t\t(justify left)\n'))
        return ('\t(symbol\n\t\t(lib_id "%s")\n\t\t(at %.2f %.2f 0)\n\t\t(unit 1)\n\t\t(exclude_from_sim no)\n\t\t(in_bom yes)\n\t\t(on_board yes)\n\t\t(dnp no)\n\t\t(uuid "%s")\n'
                % (lib, x, y, uu) + prop('Reference', ref, 1.5, -1.0, False) + prop('Value', value, 1.5, 1.0, False) + prop('Footprint', fp, 0, 0, True)
                + prop('Datasheet', '~', 0, 0, True) + prop('Description', '', 0, 0, True)
                + '\t\t(pin "1"\n\t\t\t(uuid "%s")\n\t\t)\n\t\t(pin "2"\n\t\t\t(uuid "%s")\n\t\t)\n' % (uid(), uid())
                + '\t\t(instances\n\t\t\t(project "dna-accesories"\n\t\t\t\t(path "/%s"\n\t\t\t\t\t(reference "%s")\n\t\t\t\t\t(unit 1)\n\t\t\t\t)\n\t\t\t)\n\t\t)\n\t)' % (PROJ_UUID, ref))

    uuids = {}
    items = []
    for k in range(25):
        ref = 'C%d' % (k + 1)
        x = round((200 + 17 * (k % 5)) / 1.27) * 1.27; y = round((30 + 24 * (k // 5)) / 1.27) * 1.27
        u = uid(); uuids[ref] = u
        fp, val = ('Capacitor_SMD:C_0805_2012Metric', '10uF') if k == 24 else ('Capacitor_SMD:C_0402_1005Metric', '100nF')
        items.append(part('Device:C', ref, val, fp, x, y, u))
        items.append(label('POWER', x, y - 3.81, 90)); items.append(label('GND', x, y + 3.81, 270))
    u = uid(); uuids['R1'] = u
    items.append(part('Device:R', 'R1', '100', 'Resistor_SMD:R_0402_1005Metric', 200.66, 160.02, u))
    items.append(label('CODON_START', 200.66, 160.02 - 3.81, 90)); items.append(label('DIN_FIRST', 200.66, 160.02 + 3.81, 270))
    # first LED DIN label gets the new net name
    old = '(global_label "CODON_START"\n\t\t(shape input)\n\t\t(at 54.61 35.56 180)'
    assert old in t
    t = t.replace(old, old.replace('CODON_START', 'DIN_FIRST'), 1)
    # insert before sheet_instances
    k = t.index('\t(sheet_instances')
    t = t[:k] + '\n'.join(extra + items) + '\n' + t[k:]
    open(SCH, 'w', encoding='utf8', newline='').write(t.replace('\n', '\r\n'))
    # library file
    lt = open(LIB, encoding='utf8', newline='').read().replace('\r\n', '\n')
    lt = set_pin_types(lt, types) if 'XIAO_NRF52840:102010448"' in lt else lt
    # library symbol uses its own name, apply by number on the whole file
    lt2 = open(LIB, encoding='utf8', newline='').read().replace('\r\n', '\n')
    for m in list(re.finditer(r'\(pin (\w+) (?:line|clock|inverted|inverted_clock)', lt2)):
        pass
    out = lt2
    for m in list(re.finditer(r'\(pin (\w+) (?:line|clock|inverted|inverted_clock)', lt2)):
        b = block(lt2, m.start()); num = re.search(r'\(number "([^"]+)"', b).group(1)
        if num in types:
            out = out.replace(b, b.replace('(pin %s ' % m.group(1), '(pin %s ' % types[num], 1), 1)
    open(LIB, 'w', encoding='utf8', newline='').write(out.replace('\n', '\r\n'))
    json.dump(uuids, open(ROOT + r'\gen\_part_uuids.json', 'w'))
    print('parts', len(uuids), 'nc', len(extra))


main()

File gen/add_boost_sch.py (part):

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    # rev 7: power switch (pin 1 of Q2 is G, 2 is S, 3 is D, like AO3401A in SOT-23; SW1 is a 1-position SMD slide (DIP-type) switch, pins 1 / 2)
    ('Q2', 'Transistor_FET:Q_PMOS_GSD', 'AO3401A', 'Package_TO_SOT_SMD:SOT-23', (189.23, 172.72), {'1': 'PWR_G', '2': 'BAT_RAW', '3': 'VBAT'}),
    ('R6', 'Device:R', '100k', R0402, (172.72, 172.72), {'1': 'BAT_RAW', '2': 'PWR_G'}),
    ('SW1', 'Switch:SW_SPST', 'SLIDE_SW', 'Button_Switch_SMD:SW_DIP_SPSTx01_Slide_Copal_CHS-01A_W5.08mm_P1.27mm_JPin', (172.72, 190.5), {'1': 'PWR_G', '2': 'GND'}),
]


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            ('Switch', 'SW_SPST'), ('power', 'PWR_FLAG')]
    libs = '\n'.join(lib_symbol(l, n) for l, n in need if '(symbol "%s:%s"' % (l, n) not in t)
    t = t.replace('\t(lib_symbols\n', '\t(lib_symbols\n' + libs + '\n', 1)
    # 2) U1.VUSB: the label that used to say POWER now says VUSB; U1.BAT+ gets the name VBAT
    old = '(global_label "POWER"\n\t\t(shape input)\n\t\t(at 17.78 -49.53 0)'
    assert old in t
    t = t.replace(old, old.replace('"POWER"', '"VUSB"'), 1)
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        m = re.search(r'\t\(wire\n\t\t\(pts\n\t\t\t%s\n\t\t\)\n(?:.*\n){1,6}?\t\)\n' % re.escape(pts), t)
        assert m, pts
        t = t.replace(m.group(0), '', 1)
    items.append(label('BAT_RAW', -3.81, -5.08, 90))
    # 3) parts with a label on every pin
    uuids = {}
    for ref, lib, value, fp, (x, y), nets in PARTS:
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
